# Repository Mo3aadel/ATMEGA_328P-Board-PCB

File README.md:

# ATMEGA_328P-Board-PCB
   Interfacing with Atmega 328P Uc through UART to operate three leds
   building the project circuit on a PCB

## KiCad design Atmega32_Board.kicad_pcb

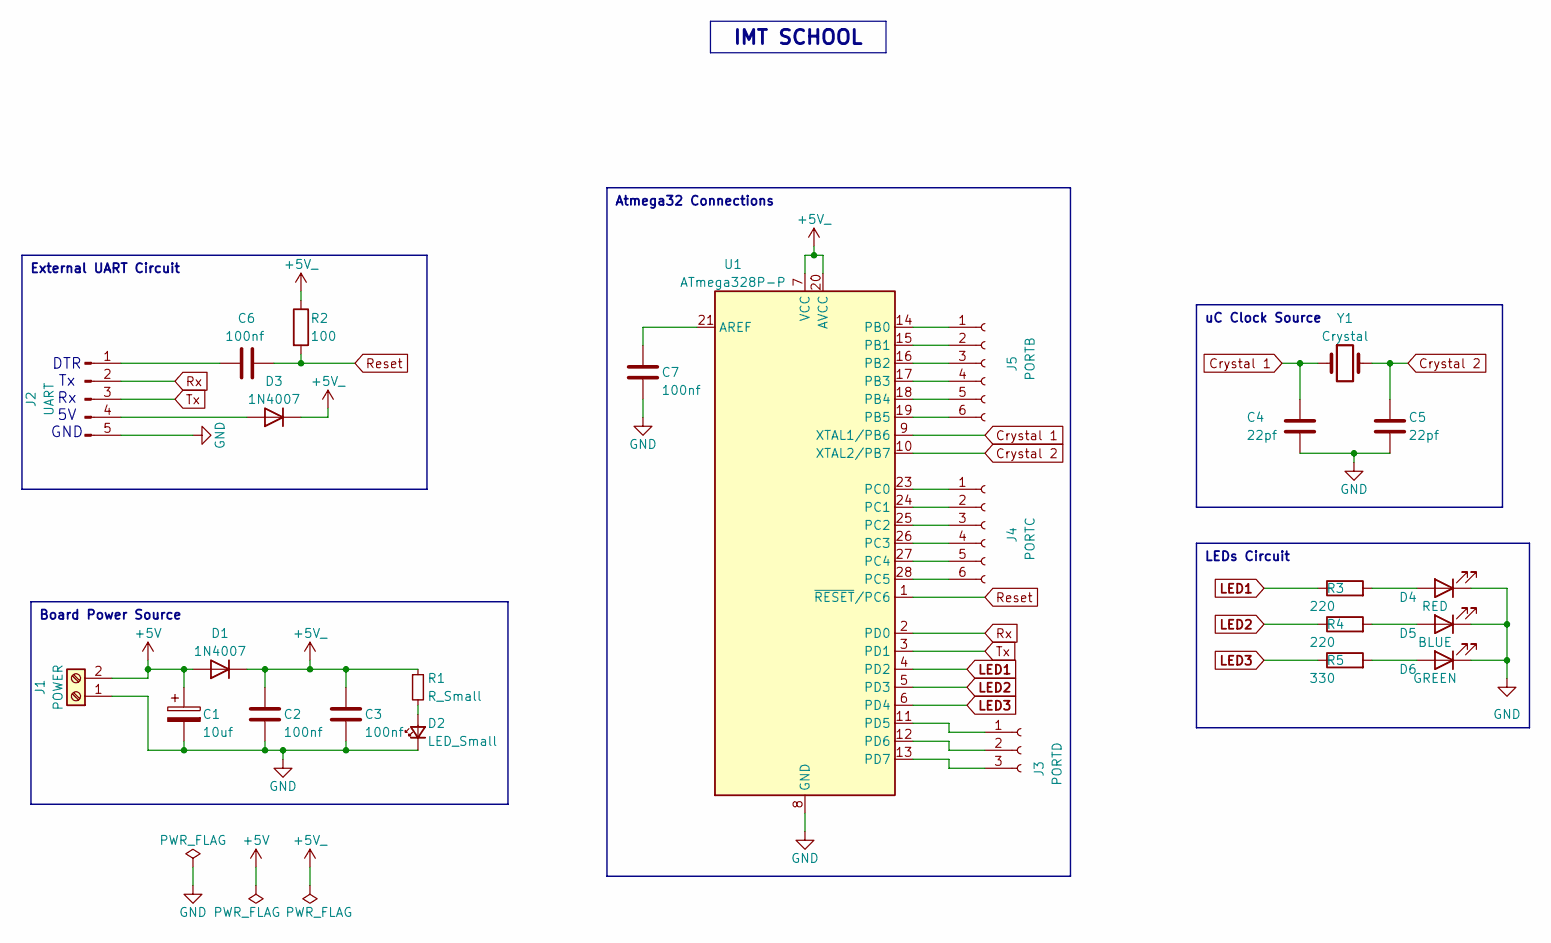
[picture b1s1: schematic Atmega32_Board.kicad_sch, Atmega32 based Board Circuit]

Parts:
C1: 10uf; CP_Radial_D5.0mm_P2.50mm
C2, C3, C6, C7: 100nf; C_Disc_D5.0mm_W2.5mm_P2.50mm
C4, C5: 22pf; C_Disc_D5.0mm_W2.5mm_P2.50mm
D1, D3: 1N4007; D_DO-41_SOD81_P10.16mm_Horizontal
D2: LED_Small; LED_1206_3216Metric_Pad1.42x1.75mm_HandSolder
D4: RED; LED_D8.0mm
D5: BLUE; LED_D8.0mm
D6: GREEN; LED_D8.0mm
J1: POWER; TerminalBlock_Phoenix_MKDS-1,5-2_1x02_P5.00mm_Horizontal
J2: UART; PinHeader_1x05_P2.54mm_Vertical
J3: PORTD; PinSocket_1x03_P2.00mm_Vertical
J4: PORTC; PinSocket_1x06_P2.00mm_Vertical
J5: PORTB; PinSocket_1x06_P2.00mm_Vertical
R1: R_Small; R_1206_3216Metric_Pad1.30x1.75mm_HandSolder
R2: 100; R_Axial_DIN0207_L6.3mm_D2.5mm_P10.16mm_Horizontal
R3, R4: 220; R_Axial_DIN0207_L6.3mm_D2.5mm_P10.16mm_Horizontal
R5: 330; R_Axial_DIN0207_L6.3mm_D2.5mm_P10.16mm_Horizontal
U1: ATmega328P-P; DIP-28_W7.62mm_Socket
Y1: Crystal; Crystal_HC49-4H_Vertical

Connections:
+5V: C1.1, D1.2 (A), J1.2
+5V_: C2.1, C3.1, D1.1 (K), D3.1 (K), R1.1, R2.1, U1.7 (VCC), U1.20 (AVCC)
Crystal 1: C4.1, U1.9 (XTAL1/PB6), Y1.1
Crystal 2: C5.1, U1.10 (XTAL2/PB7), Y1.2
GND: C1.2, C2.2, C3.2, C4.2, C5.2, C7.2, D2.1 (K), D4.1 (K), D5.1 (K), D6.1 (K), J1.1, J2.5, U1.8 (GND), U1.22 (GND)
LED1: R3.1, U1.4 (PD2)
LED2: R4.1, U1.5 (PD3)
LED3: R5.1, U1.6 (PD4)
unnamed: D2.2 (A), R1.2
unnamed: D3.2 (A), J2.4
unnamed: D4.2 (A), R3.2
unnamed: D5.2 (A), R4.2
unnamed: D6.2 (A), R5.2
unnamed: C6.1, J2.1
unnamed: J3.1, U1.11 (PD5)
unnamed: J3.2, U1.12 (PD6)
unnamed: J3.3, U1.13 (PD7)
unnamed: J4.1, U1.23 (PC0)
unnamed: J4.2, U1.24 (PC1)
unnamed: J4.3, U1.25 (PC2)
unnamed: J4.4, U1.26 (PC3)
unnamed: J4.5, U1.27 (PC4)
unnamed: J4.6, U1.28 (PC5)
unnamed: J5.1, U1.14 (PB0)
unnamed: J5.2, U1.15 (PB1)
unnamed: J5.3, U1.16 (PB2)
unnamed: J5.4, U1.17 (PB3)
unnamed: J5.5, U1.18 (PB4)
unnamed: J5.6, U1.19 (PB5)
unnamed: C7.1, U1.21 (AREF)
Reset: C6.2, R2.2, U1.1 (~RESET/PC6)
Rx: J2.2, U1.2 (PD0)
Tx: J2.3, U1.3 (PD1)

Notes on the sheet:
Atmega32 Connections
IMT SCHOOL
uC Clock Source
External UART Circuit
Board Power Source
LEDs Circuit
DTR Tx Rx 5V GND

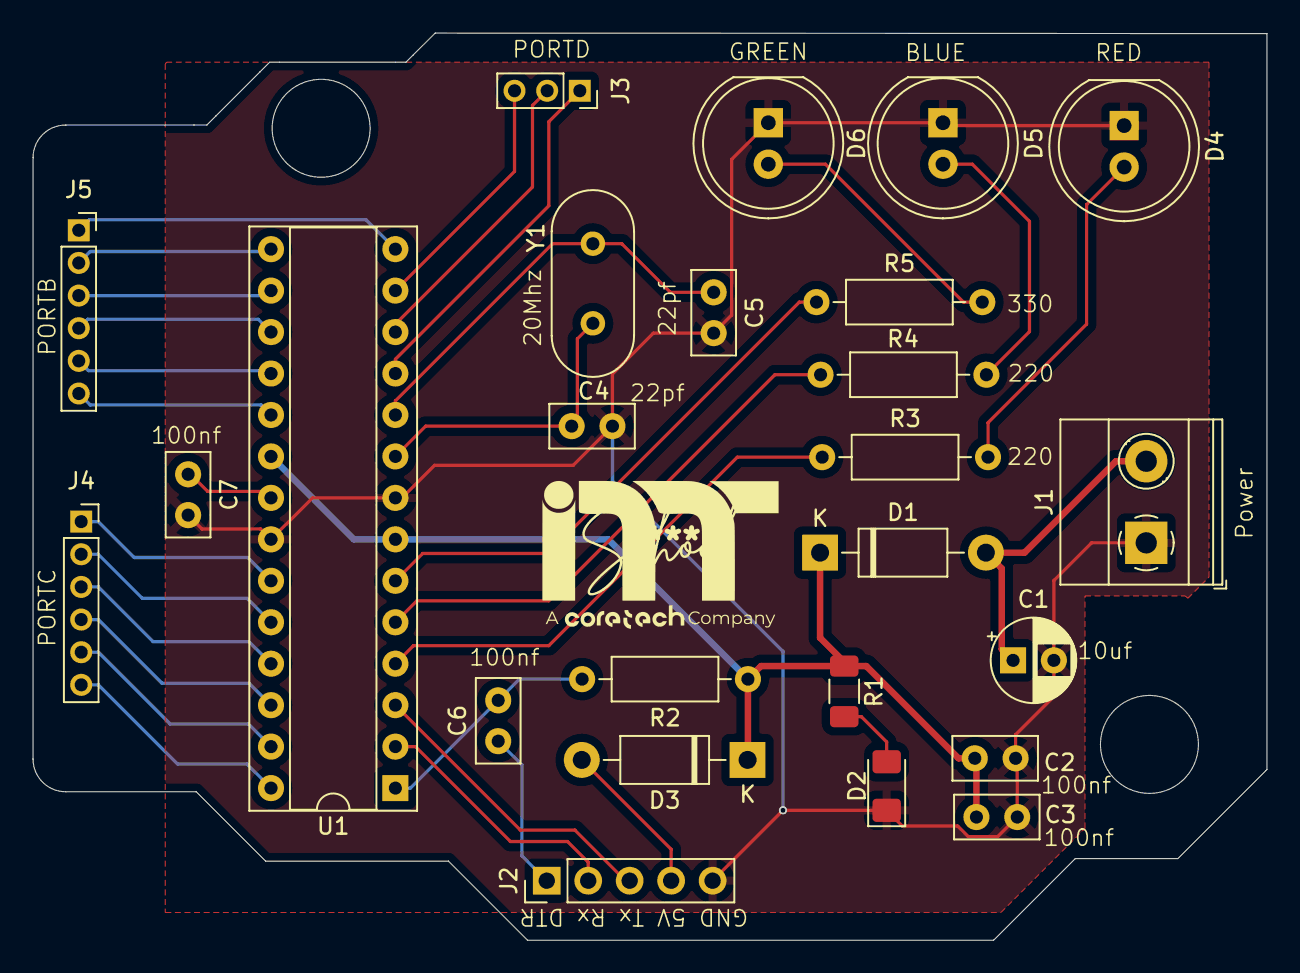
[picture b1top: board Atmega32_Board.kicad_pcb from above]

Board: 2 copper layers, 75.6 x 55.6 mm, 25 parts (0 on the bottom side), 33 nets.

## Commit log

2024-12-23 Added new Logo
2024-12-24 Added Project description
2024-12-24 changed board size
